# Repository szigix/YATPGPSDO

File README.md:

# YATPGPSDO
## Yet Another TruePosition GPSDO

This is a hardware and the corresponding firmware implemented on an STM32 BluePill board that drives a TruePosition 
GPS Disciplined Oscillator board to provide frequency reference.

For details see [my blog](https://diysquared.blogspot.com/2021/02/yatg-yet-another-trueposition-gpsdo.html).

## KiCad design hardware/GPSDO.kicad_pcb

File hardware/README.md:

# YATPGPSDO hardware
Hardware design files for Yet Another TruePosition GPSDO
EDA software: [KiCAD](https://kicad.org/)

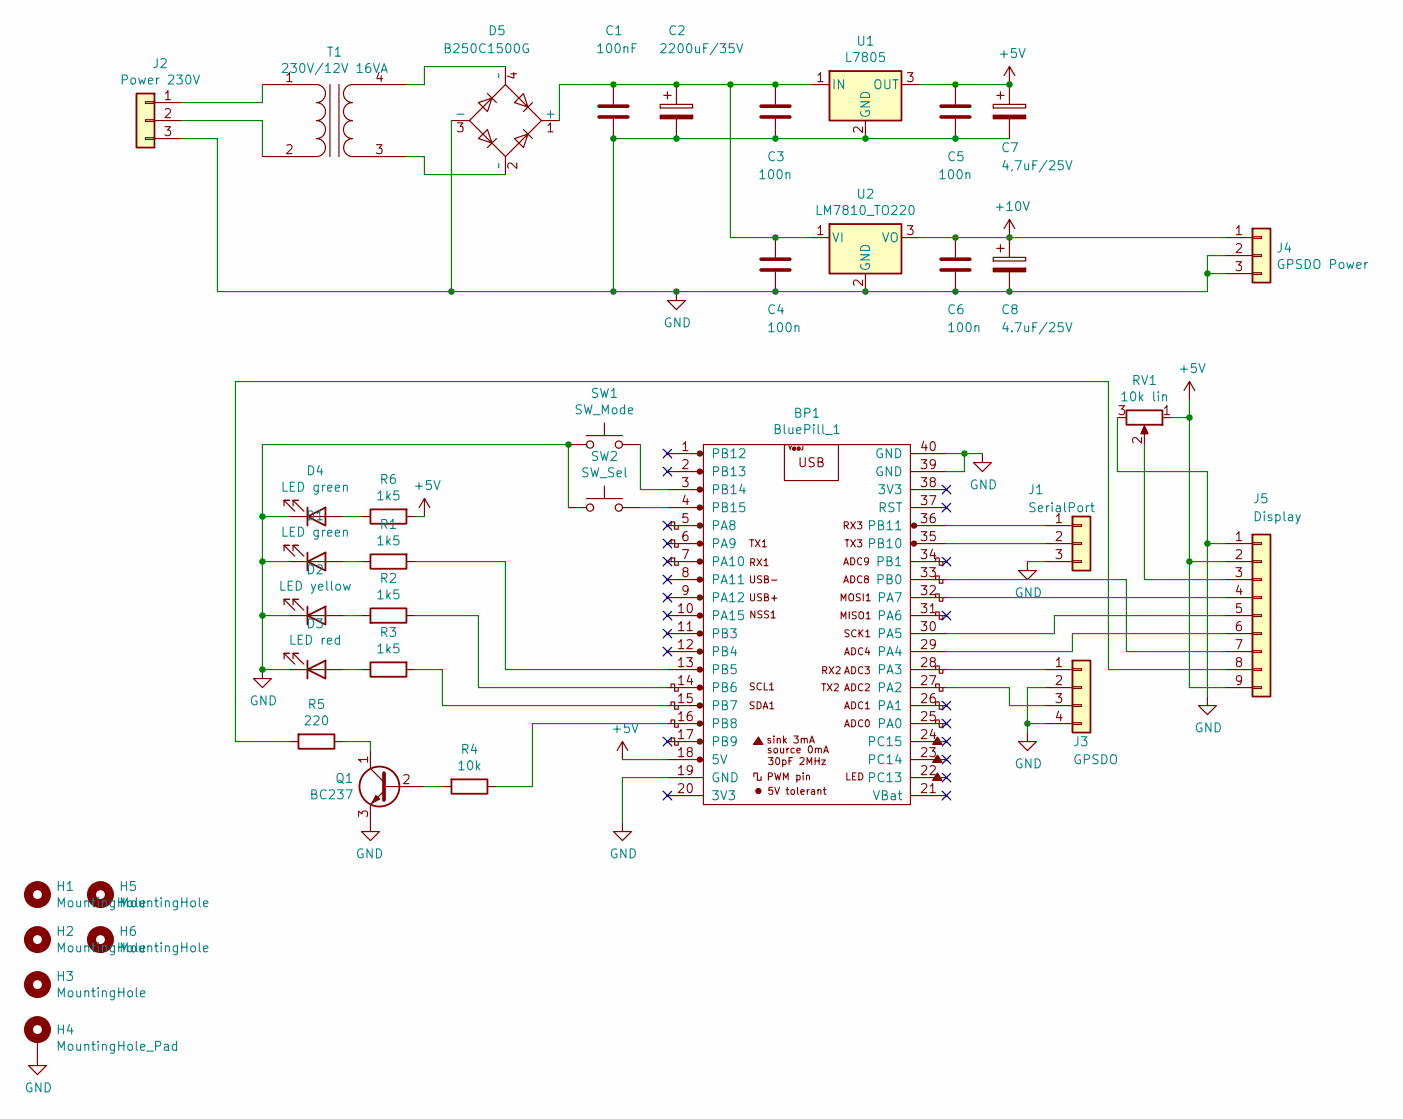
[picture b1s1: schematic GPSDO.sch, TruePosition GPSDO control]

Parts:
BP1: BluePill_1; STM32-BluePill
C1: 100nF; C_Disc_D5.0mm_W2.5mm_P2.50mm
C2: 2200uF/35V; CP_Radial_D16.0mm_P7.50mm
C3, C4, C5, C6: 100n; C_Disc_D5.0mm_W2.5mm_P2.50mm
C7: 4,7uF/25V; CP_Radial_D5.0mm_P2.00mm
C8: 4.7uF/25V; CP_Radial_D5.0mm_P2.00mm
D1, D4: LED green; PinHeader_1x02_P2.54mm_Vertical
D2: LED yellow; PinHeader_1x02_P2.54mm_Vertical
D3: LED red; PinHeader_1x02_P2.54mm_Vertical
D5: B250C1500G; Diode_Bridge_Round_D9.8mm
H1, H2, H3, H5, H6: MountingHole; MountingHole_3.2mm_M3_Pad
H4: MountingHole_Pad; MountingHole_3.2mm_M3_Pad_Via
J1: SerialPort; PinHeader_1x03_P2.54mm_Vertical
J2: Power 230V; SolderWire-1.5sqmm_1x03_P6mm_D1.7mm_OD3mm
J3: GPSDO; PinHeader_1x04_P2.54mm_Vertical
J4: GPSDO Power; PinHeader_1x03_P2.54mm_Vertical
J5: Display; PinHeader_1x09_P2.54mm_Vertical
Q1: BC237; TO-92_Inline
R1, R2, R3, R6: 1k5; R_Axial_DIN0207_L6.3mm_D2.5mm_P10.16mm_Horizontal
R4: 10k; R_Axial_DIN0207_L6.3mm_D2.5mm_P10.16mm_Horizontal
R5: 220; R_Axial_DIN0207_L6.3mm_D2.5mm_P10.16mm_Horizontal
RV1: 10k lin; Potentiometer_ACP_CA9-H2,5_Horizontal
SW1: SW_Mode; PinHeader_1x02_P2.54mm_Vertical
SW2: SW_Sel; PinHeader_1x02_P2.54mm_Vertical
T1: 230V/12V 16VA; Transforme_Gerth_Bv_54112
U1: L7805; TO-220-3_Vertical
U2: LM7810_TO220; TO-220-3_Vertical

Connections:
+5V: BP1.18 (5V), C5.1, C7.1, J5.2, J5.9, R6.2, RV1.1, U1.3 (OUT)
+10V: C6.1, C8.1, J4.1, U2.3 (VO)
GND: BP1.19 (GND), BP1.39 (GND), BP1.40 (GND), C1.2, C2.2, C3.2, C4.2, C5.2, C6.2, C7.2, C8.2, D1.1 (K), D2.1 (K), D3.1 (K), D4.1 (K), D5.3 (-), H4.1, J1.3, J2.3, J3.2, J3.4, J4.2, J4.3, J5.1, Q1.3 (E), RV1.3, SW1.2, SW2.2, U1.2 (GND), U2.2 (GND)
unnamed: BP1.3 (PB14), SW1.1
unnamed: BP1.4 (PB15), SW2.1
unnamed: BP1.13 (PB5), R1.2
unnamed: BP1.14 (PB6), R2.1
unnamed: BP1.15 (PB7), R3.2
unnamed: BP1.16 (PB8), R4.1
unnamed: BP1.27 (PA2), J3.3
unnamed: BP1.28 (PA3), J3.1
unnamed: BP1.29 (PA4), J5.6
unnamed: BP1.30 (PA5), J5.5
unnamed: BP1.32 (PA7), J5.4
unnamed: BP1.33 (PB0), J5.7
unnamed: BP1.35 (PB10), J1.2
unnamed: BP1.36 (PB11), J1.1
unnamed: C1.1, C2.1, C3.1, C4.1, D5.1 (+), U1.1 (IN), U2.1 (VI)
unnamed: D1.2 (A), R1.1
unnamed: D2.2 (A), R2.2
unnamed: D3.2 (A), R3.1
unnamed: D4.2 (A), R6.1
unnamed: D5.2 (~~), T1.3 (SA)
unnamed: D5.4 (~~), T1.4 (SB)
unnamed: J2.1, T1.1 (AA)
unnamed: J2.2, T1.2 (AB)
unnamed: J5.3, RV1.2
unnamed: J5.8, R5.2
unnamed: Q1.1 (C), R5.1
unnamed: Q1.2 (B), R4.2

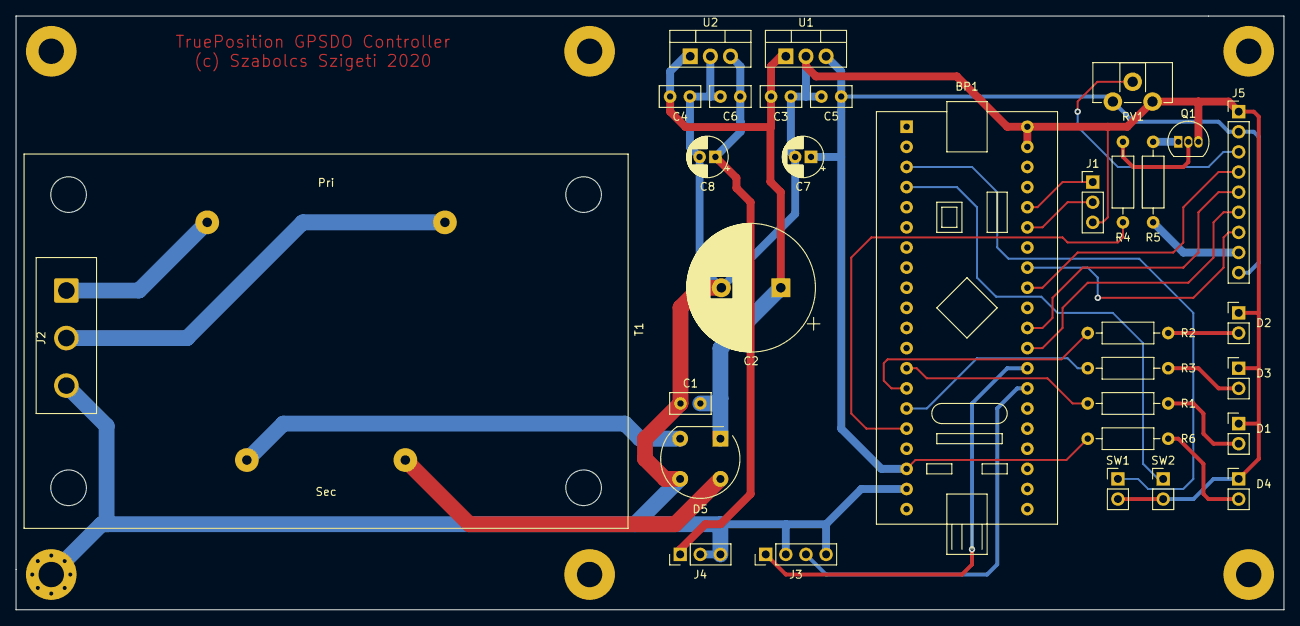
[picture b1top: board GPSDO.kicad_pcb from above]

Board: 2 copper layers, 160.0 x 74.9 mm, 38 parts (0 on the bottom side), 30 nets.

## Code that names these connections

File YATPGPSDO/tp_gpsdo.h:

/*
   (c) Copyright Szabolcs Szigeti 2020-2021

   Redistribution under GPL V3. See the LICENSE file for details.

*/
/*
   Configuration section
*/

#define VERSION "V1.15 2022/06/04"

#define GPSDO_BAUD  9600     // GPSDO serial speed: 9600 do not change

#define BTN_MODE  PB15       // mode button
#define BTN_SEL   PB14       // select button
#define LED_ONBOARD  PC13    // BluePill onboard LED - used for heartbeat indication
#define LED_HOLDOVER PB6     // Yellow LED for holdover
#define LED_LOCK  PB5        // Green LED for lock
#define LED_ALARM PB7        // Red LED for failure
#define LED_BACKLIGHT PB8    // Port for controlling display backlight

#define EEConfAddr  0x00      // Config address in EEPROM

#define DEBOUNCE  40         // Button debounce time in miliseconds. Shorter presses are not registred.
#define SHORTPRESS 500       // Limit for long button press.

#define NOMSGTIME 10000       // timeout if no GPS message for 10 seconds
#define PERIODICMSG 60000     // Position report every 60 seconds
#define BLINKTIME 500         // How fast things on the LEDs and display blink.
#define BACKLIGTHOFF  10000   // Backlight for 10 sec in auto mode
#define POPUPDURATION 5000    // Duration of popup messages
#define POPUPLEN  13          // Max popup text length

#define TIMEOFFSET  315964800L   // Magic correction for the 10 years off time from the gps. My TP reports time about 10 years off

#define NUMSAT 8               // Max number of satellites to track
#define MSGMAX  60             // Max msg size in chars

enum DisplayModes {STATUS, TIME, SATS, POSITION, CONFIG, ENDOFMODES};     // Display screens to flip with the Mode button
enum MenuModes {SHOWSURVEY, SETSURVEY, SETBACKLIGHT, SETOFFSET, SAVECONFIG, TRAINO}; // Various sub modes for the sreens

void ProcessGPSMsg();
bool GetGPSMsg();

void SetupDisplay();
void UpdateDisplay();
void handleButtons();
void PressBtnMode(int);
void PressBtnSel(int);
void handleLEDs();
void nextDisplay();
void showPopup(const char* text);

unsigned long millis();

/*
   System comfguration
*/
struct CONFIG {
  int timeoffset;             // Timezone settings in hours
  unsigned int surveytime;    // Default survey time
  unsigned int backlight;     // Backlight mode
};

/*
   Data from the CLOCK message
*/
struct CLOCK {
  int year;
  int month;
  int day;
  int hour;
  int minute;
  int second;
  int weekday;
  int quality;                // Time quality reported by the GPS
  uint32_t ticks;             // Unixtime ticks
};

/*
   General status of the system, mostly form the STATUS, EXTATUS messages
*/
struct STATUS {
  bool tenmhz;              // 10MHz is good. Is it ever bad???
  bool onepps;              // 1PPS id good. Same as above
  bool antenna;             // Antenna is correctly connected.
  int holdover;             // Holdover time
  int status;               // TruePosition status
  bool initialized;         // Has the TruePosition booted up?
  int nsats;                // Number of sats seen
  int tsats;                // Number of sats tracked
  float dop;                // DOP value
  float temp;               // Temperature of the unit
  int phaseoffset;          // Phase offset
  long lat;                 // Latitude
  long lon;                 // Longitude
  int elev;                 // Elevation
  bool surveying;           // Survey is in progress
  bool surveyed;            // Survey was run since last reboot
  int surveytime;           // Survey length
  float dac;                // DAC value for the OCXO steering
  char TPversion[11];       // Version string from the TruePosition board
  uint32_t lockedSince;     // Start time of current locked status, 0 if not locked
};

/*
   Data on satellites
*/
struct SATS {
  int satnum;               // Satellite PRN number
  int elevation;            // Elevation in degrees
  int azimuth;              // Azimuth in degrees
  int snr;                  // SNR value
  bool iswaas;              // Is it a WAAS/EGNOS sat?
};

/*
   Current alerts
*/
struct ALERTS {
  bool tenmhz;              // 10MHz is bad
  bool onepps;              // 1PPS is bad
  bool antenna;             // Antenna not detected
  bool nogps;               // Lost connection with TruePosition board
};

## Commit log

2021-02-20 Initial upload
2021-02-23 Fixed DAC and Temp resolution
2021-02-23 Removed the useless DEBUG code
2021-02-23 Indicate if survey was run since poweron.
2021-02-24 Removed position reload
    Removed position reload, as not useful.
    Added OCXO training.
    Some display changes.
    Other small changes .
2021-03-08 Tweak satellite snr display and fix typos
2021-04-03 Fix default survey time
    Some code tidy-up with survey time.
    Some typos squashed.
    Fixing default survey time not being saved.
2021-07-06 Changed to pre-drawn clock face
    Changed the analog clock face to be a pre drawn bitmap, instead of drawing on the fly. Looks a bit better, but not perfect.
2021-07-14 Fix DOP display
    Fix DOP display, it is float.
    Fix typos.
    Small code cleanups.
2022-03-15 Uploaded Gerbers
    Some typos fixed, Gerbers added
2022-04-09 Analog clock beautify
    Fix the very ugly analog clock display. It had pixel offset erros and the clockface bitmap was bad.
    It sucks much less now.
2022-06-04 Popup display
    Removed the kludge for the save config display and added a popup instead.
2022-06-04 Fix function proto
    Minor fix, no new version
